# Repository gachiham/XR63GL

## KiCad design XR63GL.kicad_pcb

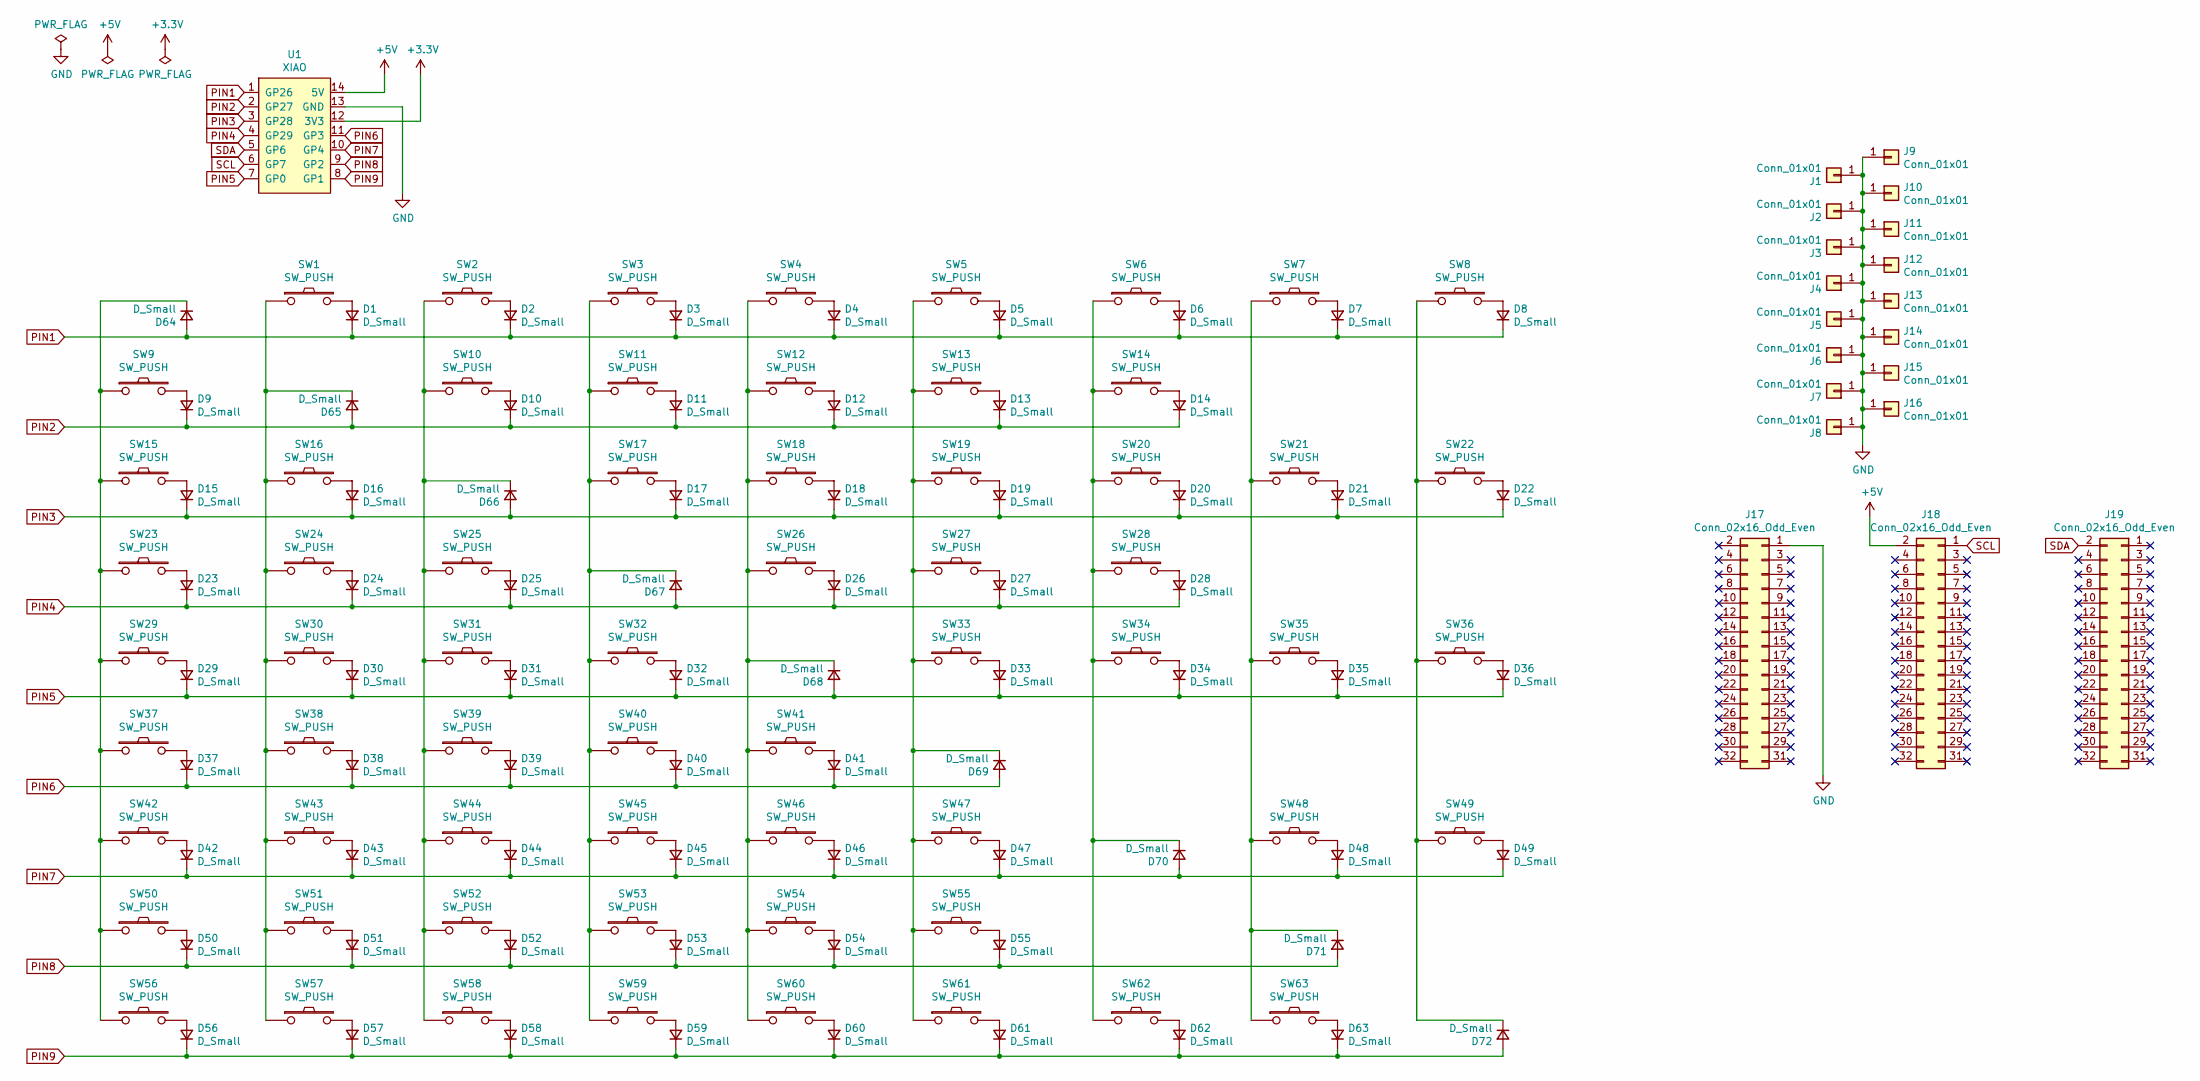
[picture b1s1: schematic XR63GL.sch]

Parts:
D1, D2, D3, D4, D5, D6, D7, D8, D9, D10, D11, D12, D13, D14, D15, D16, D17, D18, D19, D20, D21, D22, D23, D24, D25, D26, D27, D28, D29, D30, D31, D32, D33, D34, D35, D36, D37, D38, D39, D40, D41, D42, D43, D44, D45, D46, D47, D48, D49, D50, D51, D52, D53, D54, D55, D56, D57, D58, D59, D60, D61, D62, D63, D64, D65, D66, D67, D68, D69, D70, D71, D72: D_Small; D3_SMD_Single_side_rev
J1, J2, J3, J4, J5, J6, J7, J8, J9, J10, J11, J12, J13, J14, J15, J16: Conn_01x01; HOLE_m2_Outline_Fab
J17, J18, J19: Conn_02x16_Odd_Even; PinSocket_2x16_P2.54mm_Vertical
SW1, SW2, SW3, SW4, SW5, SW6, SW7, SW8, SW9, SW10, SW11, SW12, SW13, SW16, SW17, SW18, SW19, SW20, SW21, SW22, SW23, SW24, SW25, SW26, SW27, SW30, SW31, SW32, SW33, SW34, SW35, SW36, SW37, SW38, SW39, SW40, SW43, SW44, SW45, SW46, SW47, SW48, SW49, SW50, SW51, SW52, SW54, SW55, SW62, SW63: SW_PUSH; CherryMX_Hotswap_1.0u_One_Side_Pad_Expansion
SW14: SW_PUSH; CherryMX_Hotswap_2.0u_One_Side_Pad_Expansion
SW15, SW28: SW_PUSH; CherryMX_Hotswap_1.5u_One_Side_Pad_Expansion
SW29: SW_PUSH; CherryMX_Hotswap_1.75u_One_Side_Pad_Expansion
SW41, SW42: SW_PUSH; CherryMX_Hotswap_2.25u_One_Side_Pad_Expansion
SW53, SW56, SW57, SW58, SW60, SW61: SW_PUSH; CherryMX_Hotswap_1.25u_One_Side_Pad_Expansion
SW59: SW_PUSH; CherryMX_Hotswap_6.25u_One_Side_Pad_Expansion
U1: XIAO; XIAO_Pin_Header

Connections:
+3V3: U1.12 (3V3)
+5V: J18.2, U1.14 (5V)
GND: J1.1, J2.1, J3.1, J4.1, J5.1, J6.1, J7.1, J8.1, J9.1, J10.1, J11.1, J12.1, J13.1, J14.1, J15.1, J16.1, J17.1, U1.13 (GND)
unnamed: D1.2 (A), SW1.2
unnamed: D2.2 (A), SW2.2
unnamed: D3.2 (A), SW3.2
unnamed: D4.2 (A), SW4.2
unnamed: D5.2 (A), SW5.2
unnamed: D6.2 (A), SW6.2
unnamed: D7.2 (A), SW7.2
unnamed: D8.2 (A), SW8.2
unnamed: D9.2 (A), SW9.2
unnamed: D10.2 (A), SW10.2
unnamed: D11.2 (A), SW11.2
unnamed: D12.2 (A), SW12.2
unnamed: D13.2 (A), SW13.2
unnamed: D14.2 (A), SW14.2
unnamed: D15.2 (A), SW15.2
unnamed: D16.2 (A), SW16.2
unnamed: D17.2 (A), SW17.2
unnamed: D18.2 (A), SW18.2
unnamed: D19.2 (A), SW19.2
unnamed: D20.2 (A), SW20.2
unnamed: D21.2 (A), SW21.2
unnamed: D22.2 (A), SW22.2
unnamed: D23.2 (A), SW23.2
unnamed: D24.2 (A), SW24.2
unnamed: D25.2 (A), SW25.2
unnamed: D26.2 (A), SW26.2
unnamed: D27.2 (A), SW27.2
unnamed: D28.2 (A), SW28.2
unnamed: D29.2 (A), SW29.2
unnamed: D30.2 (A), SW30.2
unnamed: D31.2 (A), SW31.2
unnamed: D32.2 (A), SW32.2
unnamed: D33.2 (A), SW33.2
unnamed: D34.2 (A), SW34.2
unnamed: D35.2 (A), SW35.2
unnamed: D36.2 (A), SW36.2
unnamed: D37.2 (A), SW37.2
unnamed: D38.2 (A), SW38.2
unnamed: D39.2 (A), SW39.2
unnamed: D40.2 (A), SW40.2
unnamed: D41.2 (A), SW41.2
unnamed: D42.2 (A), SW42.2
unnamed: D43.2 (A), SW43.2
unnamed: D44.2 (A), SW44.2
unnamed: D45.2 (A), SW45.2
unnamed: D46.2 (A), SW46.2
unnamed: D47.2 (A), SW47.2
unnamed: D48.2 (A), SW48.2
unnamed: D49.2 (A), SW49.2
unnamed: D50.2 (A), SW50.2
unnamed: D51.2 (A), SW51.2
unnamed: D52.2 (A), SW52.2
unnamed: D53.2 (A), SW53.2
unnamed: D54.2 (A), SW54.2
unnamed: D55.2 (A), SW55.2
unnamed: D56.2 (A), SW56.2
unnamed: D57.2 (A), SW57.2
unnamed: D58.2 (A), SW58.2
unnamed: D59.2 (A), SW59.2
unnamed: D60.2 (A), SW60.2
unnamed: D61.2 (A), SW61.2
unnamed: D62.2 (A), SW62.2
unnamed: D63.2 (A), SW63.2
unnamed: D64.1 (K), SW9.1, SW15.1, SW23.1, SW29.1, SW37.1, SW42.1, SW50.1, SW56.1
unnamed: D65.1 (K), SW1.1, SW16.1, SW24.1, SW30.1, SW38.1, SW43.1, SW51.1, SW57.1
unnamed: D66.1 (K), SW2.1, SW10.1, SW25.1, SW31.1, SW39.1, SW44.1, SW52.1, SW58.1
unnamed: D67.1 (K), SW3.1, SW11.1, SW17.1, SW32.1, SW40.1, SW45.1, SW53.1, SW59.1
unnamed: D68.1 (K), SW4.1, SW12.1, SW18.1, SW26.1, SW41.1, SW46.1, SW54.1, SW60.1
unnamed: D69.1 (K), SW5.1, SW13.1, SW19.1, SW27.1, SW33.1, SW47.1, SW55.1, SW61.1
unnamed: D70.1 (K), SW6.1, SW14.1, SW20.1, SW28.1, SW34.1, SW62.1
unnamed: D71.1 (K), SW7.1, SW21.1, SW35.1, SW48.1, SW63.1
unnamed: D72.1 (K), SW8.1, SW22.1, SW36.1, SW49.1
PIN1: D1.1 (K), D2.1 (K), D3.1 (K), D4.1 (K), D5.1 (K), D6.1 (K), D7.1 (K), D8.1 (K), D64.2 (A), U1.1 (GP26)
PIN2: D9.1 (K), D10.1 (K), D11.1 (K), D12.1 (K), D13.1 (K), D14.1 (K), D65.2 (A), U1.2 (GP27)
PIN3: D15.1 (K), D16.1 (K), D17.1 (K), D18.1 (K), D19.1 (K), D20.1 (K), D21.1 (K), D22.1 (K), D66.2 (A), U1.3 (GP28)
PIN4: D23.1 (K), D24.1 (K), D25.1 (K), D26.1 (K), D27.1 (K), D28.1 (K), D67.2 (A), U1.4 (GP29)
PIN5: D29.1 (K), D30.1 (K), D31.1 (K), D32.1 (K), D33.1 (K), D34.1 (K), D35.1 (K), D36.1 (K), D68.2 (A), U1.7 (GP0)
PIN6: D37.1 (K), D38.1 (K), D39.1 (K), D40.1 (K), D41.1 (K), D69.2 (A), U1.11 (GP3)
PIN7: D42.1 (K), D43.1 (K), D44.1 (K), D45.1 (K), D46.1 (K), D47.1 (K), D48.1 (K), D49.1 (K), D70.2 (A), U1.10 (GP4)
PIN8: D50.1 (K), D51.1 (K), D52.1 (K), D53.1 (K), D54.1 (K), D55.1 (K), D71.2 (A), U1.9 (GP2)
PIN9: D56.1 (K), D57.1 (K), D58.1 (K), D59.1 (K), D60.1 (K), D61.1 (K), D62.1 (K), D63.1 (K), D72.2 (A), U1.8 (GP1)
SCL: J18.1, U1.6 (GP7)
SDA: J19.2, U1.5 (GP6)

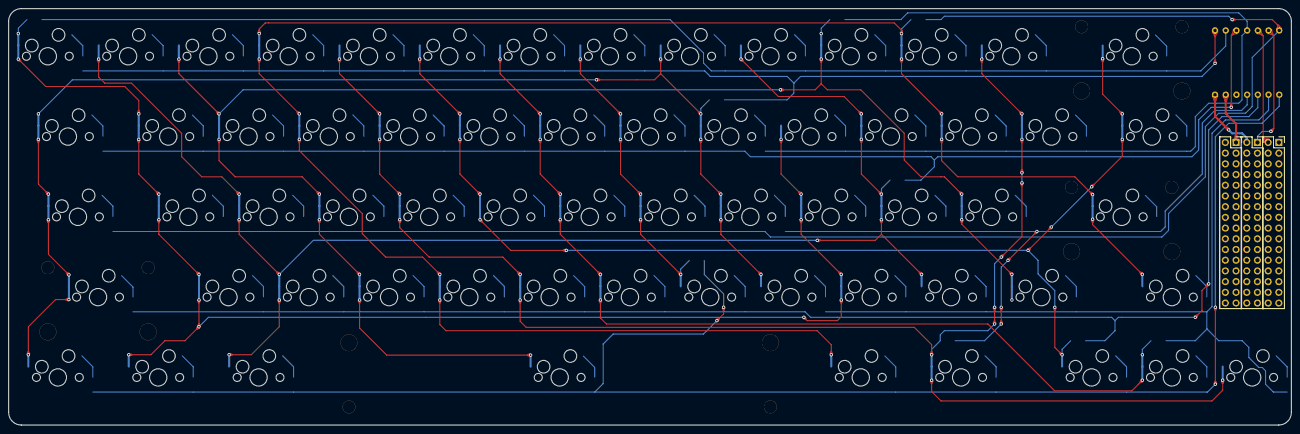
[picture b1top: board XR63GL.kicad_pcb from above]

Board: 2 copper layers, 304.4 x 98.8 mm, 155 parts (1 on the bottom side), 85 nets.

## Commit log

2022-09-20 Create LICENSE
2022-09-21 v1.0
